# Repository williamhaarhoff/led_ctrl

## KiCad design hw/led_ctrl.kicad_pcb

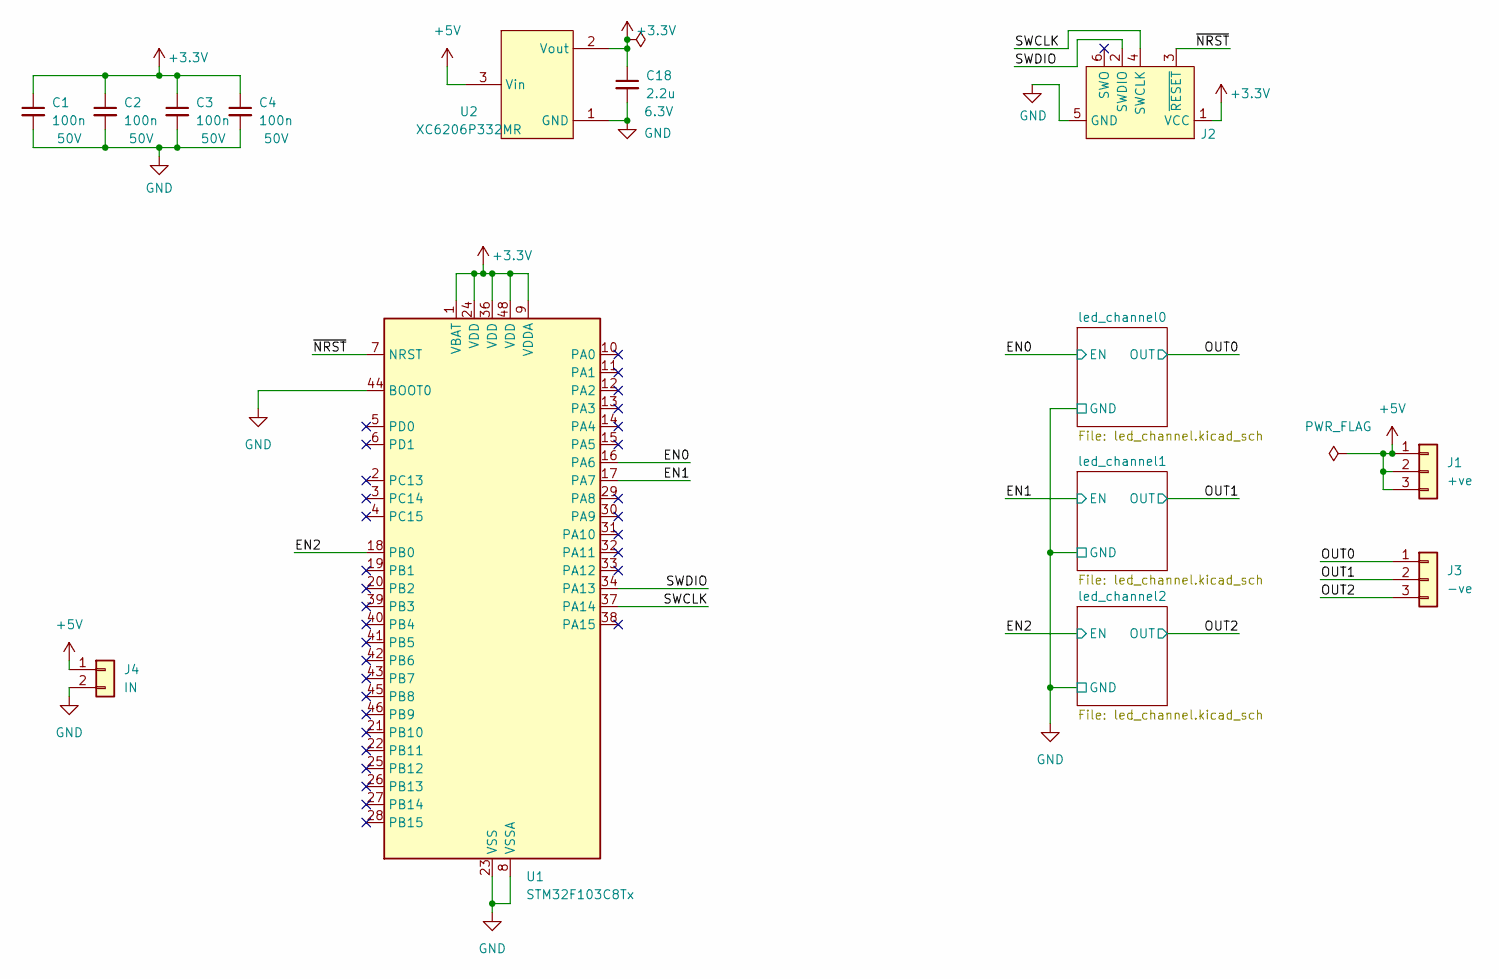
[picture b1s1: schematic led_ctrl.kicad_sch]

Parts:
C1, C2, C3, C4: 100n; C_0402_1005Metric; Rating 50V; LCSC C307331
C18: 2.2u; C_0402_1005Metric; Rating 6.3V; LCSC C12530
J1: +ve; PinHeader_1x03_P2.54mm_Vertical
J2: Tag Connect; Tag-Connect_TC2030-IDC-NL_2x03_P1.27mm_Vertical
J3: -ve; PinHeader_1x03_P2.54mm_Vertical
J4: IN; PinHeader_1x02_P2.54mm_Vertical
U1: STM32F103C8Tx; LQFP-48_7x7mm_P0.5mm; LCSC C8734
U2: XC6206P332MR; SOT-23-3_L2.9-W1.6-P1.90-LS2.8-BR; LCSC Part C5446

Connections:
+3.3V: C1.1, C2.1, C3.1, C4.1, C18.1, J2.1 (VCC), U1.1 (VBAT), U1.9 (VDDA), U1.24 (VDD), U1.36 (VDD), U1.48 (VDD), U2.2 (Vout)
+5V: J1.1, J1.2, J1.3, J4.1, U2.3 (Vin)
/EN0: U1.16 (PA6); also elsewhere on the board
/EN1: U1.17 (PA7); also elsewhere on the board
/EN2: U1.18 (PB0); also elsewhere on the board
/OUT0: J3.1; also elsewhere on the board
/OUT1: J3.2; also elsewhere on the board
/OUT2: J3.3; also elsewhere on the board
/SWCLK: J2.4 (SWCLK), U1.37 (PA14)
/SWDIO: J2.2 (SWDIO), U1.34 (PA13)
/~NRST: J2.3 (~RESET), U1.7 (NRST)
GND: C1.2, C2.2, C3.2, C4.2, C18.2, J2.5 (GND), J4.2, U1.8 (VSSA), U1.23 (VSS), U1.35 (VSS), U1.44 (BOOT0), U1.47 (VSS), U2.1 (GND); also elsewhere on the board

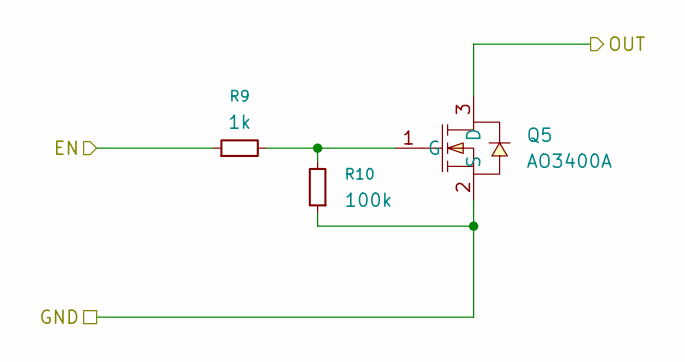
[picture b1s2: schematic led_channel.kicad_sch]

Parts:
Q5: AO3400A; SOT-23-3_L2.9-W1.3-P1.90-LS2.4-BR; LCSC Part C20917
R9: 1k; R_0805_2012Metric; LCSC C17513
R10: 100k; R_0805_2012Metric; LCSC C149504

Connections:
/EN0: R9.1; also elsewhere on the board
/OUT0: Q5.3 (D); also elsewhere on the board
GND: Q5.2 (S), R10.1; also elsewhere on the board
unnamed: Q5.1 (G), R9.2, R10.2

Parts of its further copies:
Q6, Q7: AO3400A; SOT-23-3_L2.9-W1.3-P1.90-LS2.4-BR; LCSC Part C20917
R11, R13: 1k; R_0805_2012Metric; LCSC C17513
R12, R14: 100k; R_0805_2012Metric; LCSC C149504

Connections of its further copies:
/EN1: R11.1; also elsewhere on the board
/EN2: R13.1; also elsewhere on the board
/OUT1: Q6.3 (D); also elsewhere on the board
/OUT2: Q7.3 (D); also elsewhere on the board
GND: Q6.2 (S), Q7.2 (S), R12.1, R14.1; also elsewhere on the board
unnamed: Q6.1 (G), R11.2, R12.2
unnamed: Q7.1 (G), R13.2, R14.2

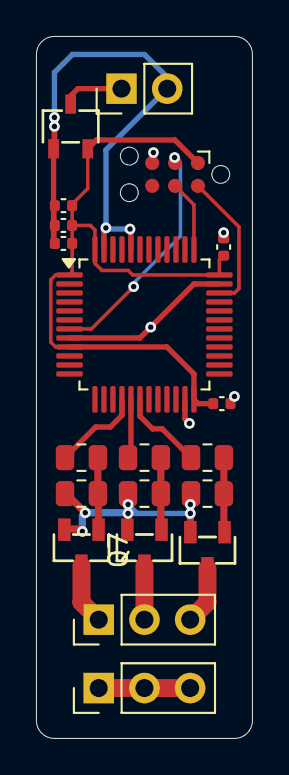
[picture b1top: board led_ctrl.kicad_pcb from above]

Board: 2 copper layers, 12.0 x 39.0 mm, 20 parts (0 on the bottom side), 15 nets.

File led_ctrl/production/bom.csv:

Designator,Footprint,Quantity,Value,LCSC Part #
"C1, C2, C3, C4",0402,4,100n,C307331
C18,0402,1,2.2u,C12530
J1,PinHeader_1x03_P2.54mm_Vertical,1,+ve,
J3,PinHeader_1x03_P2.54mm_Vertical,1,-ve,
J4,PinHeader_1x02_P2.54mm_Vertical,1,IN,
"Q5, Q6, Q7",SOT-23-3_L2.9-W1.3-P1.90-LS2.4-BR,3,AO3400A,C20917
"R10, R12, R14",0805,3,100k,C149504
"R11, R13, R9",0805,3,1k,C17513
U1,LQFP-48_7x7mm_P0.5mm,1,STM32F103C8Tx,C8734
U2,SOT-23-3_L2.9-W1.6-P1.90-LS2.8-BR,1,XC6206P332MR,C5446

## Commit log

2026-03-26 Simple board with 3 channels
2026-03-26 Rename subfolder to hw (hardware)
2026-03-26 Basic infrastructure setup
2026-03-26 Failing to assemble
2026-03-26 Its working!
2026-04-12 Actually reproducible now that rust-toolchain is pinned
